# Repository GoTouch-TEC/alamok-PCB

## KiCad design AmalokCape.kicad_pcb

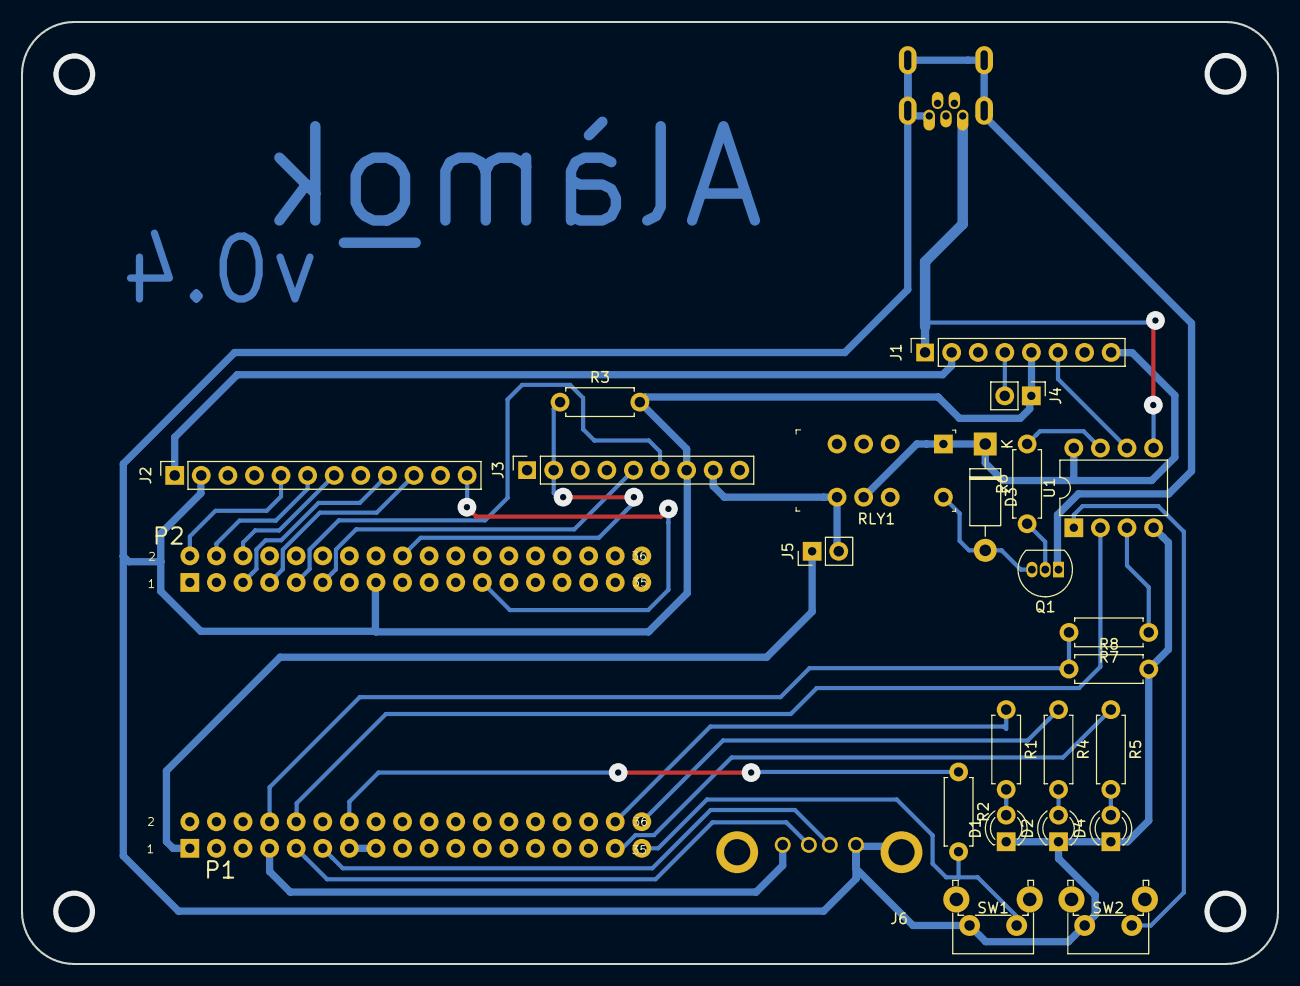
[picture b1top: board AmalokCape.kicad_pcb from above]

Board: 4 copper layers, 120.0 x 90.0 mm, 26 parts (0 on the bottom side), 35 nets.

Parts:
D1: LED1; LED_D3.0mm
D2: LED2; LED_D3.0mm
D3: 1N4001; D_DO-41_SOD81_P10.16mm_Horizontal
D4: LED3; LED_D3.0mm
J1: PowerBoost_1000C; PinSocket_1x08_P2.54mm_Vertical
J2: FONA800H; PinSocket_1x12_P2.54mm_Vertical
J3: UltimateGPS; PinSocket_1x09_P2.54mm_Vertical
J4, J5: Conn_01x02_Male; PinHeader_1x02_P2.54mm_Vertical
J6: USB_A; USB_A_0482580001
J8: USB_B_Mini; USB_Mini_B_Female_XM7D-0512
P1, P2: TH-2X18-(35MIL-DIA)-W_O-SILK
Q1: 2N3904; TO-92_Inline
R1, R4, R5: 330Ohm; R_Axial_DIN0207_L6.3mm_D2.5mm_P7.62mm_Horizontal
R2, R3, R6: 1kOhm; R_Axial_DIN0207_L6.3mm_D2.5mm_P7.62mm_Horizontal
R7: 3kOhm; R_Axial_DIN0207_L6.3mm_D2.5mm_P7.62mm_Horizontal
R8: 5kOhm; R_Axial_DIN0207_L6.3mm_D2.5mm_P7.62mm_Horizontal
RLY1: EC2-5NU; Relay_THT_EC2
SW1, SW2: SW_Push; SW_Tactile_SPST_Angled_PTS645Vx83-2LFS
U1: ATtiny85-20PU; DIP-8_W7.62mm

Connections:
/5Vin: D3.1, J1.8, RLY1.1, RLY1.9, U1.8
/(U1.A1)PWM0A: P1.36, R4.1
/(U1.A2)PRU-0.1: P1.33, R5.1
/(U1.A11)I2C1.SDA: J3.5, P2.11
/(U1.A13)SPI0.CLK: P1.8, R7.2, R8.1
/(U1.B11)I2C1.SCL: J3.6, P2.9
/(U1.B13)SPI0.MISO: P1.10, U1.2
/(U1.F1): P1.35, R2.2, SW1.1
/(U1.L15)USB1.D+: J6.3, P1.11
/(U1.L16)USB1.D-: J6.2, P1.9
/(U1.P7)PRU-0.15: J3.2, P2.18, R3.1
/(U1.P15)UART4.RX: J2.9, P2.5
/(U1.R5)GPIO-0.26: P1.34, R1.1
/(U1.R15): J2.6, P2.4
/(U1.R16)UART4.TX: J2.10, P2.7
/(U1.T15): J2.7, P2.6
/(U1.T16): J2.5, P2.2
/EN: J1.4, J4.2
/LBO: J1.6, U1.6
/Relay: R6.2, U1.7
/Reset: SW2.1, U1.1
/Vbat: J1.2, J2.1
/VinPB: J5.1, P1.1
/Vusb: J1.1, J8.1, U1.5
GND: D1.1, D2.1, D4.1, J1.5, J1.7, J2.2, J3.7, J4.1, J6.4, J6.5, J8.5, J8.6, P1.13, P1.15, P1.16, P1.22, P2.15, P2.21, Q1.1, R3.2, R8.2, SW1.2, SW2.2, U1.4
unnamed: D1.2, R1.2
unnamed: D2.2, R4.2
unnamed: D3.2, Q1.3, RLY1.12
unnamed: D4.2, R5.2
unnamed: Q1.2, R6.1
unnamed: R7.1, U1.3
SYS_5V: P1.24, P2.13
USB_DC: J6.1, P1.7
VDD_3V3B: J2.12, P1.14, P2.23, R2.1
VDD_5V: J3.8, J5.2, RLY1.8

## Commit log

2018-05-07 [new] gitignore
2018-05-07 [new] Schematic design [new] Adafruit modules symbols [new] PCB design
2018-05-24 [add] PowerManager circuit
2018-05-24 [add] 2D PCB model (in progress)
2018-05-25 [add] PCB guide and connectors footprints
2018-05-25 [add] Power management circuit [add] New PCB footprints distribution
2018-05-25 [add] V0.4 layout
2018-05-27 [fix] USB connector pins Vias size
